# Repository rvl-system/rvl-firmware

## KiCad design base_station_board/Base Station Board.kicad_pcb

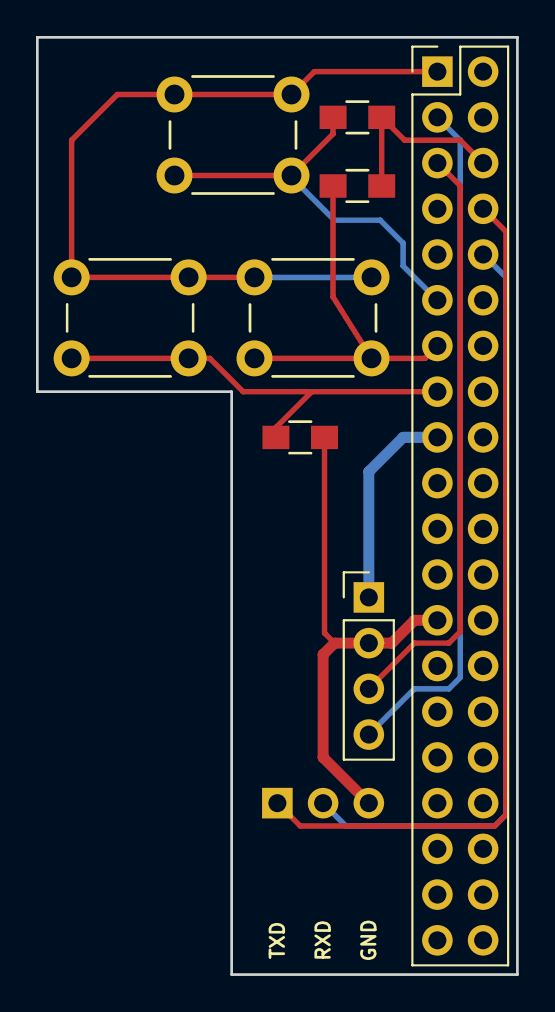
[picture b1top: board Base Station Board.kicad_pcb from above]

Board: 2 copper layers, 26.7 x 52.1 mm, 9 parts (1 on the bottom side), 11 nets.

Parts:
P1: LCD; Pin_Header_Straight_1x04_Pitch2.54mm
P2: Serial; Pin_Header_Angled_1x03_Pitch2.54mm
P3: Raspberry Pi; Pin_Header_Straight_2x20_Pitch2.54mm
R1, R2, R3: 1k; R_0805_HandSoldering
SW1, SW2, SW3: SPST; SW_PUSH_6mm

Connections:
unnamed: P1.1, P3.17
unnamed: P1.2, P2.3, P3.25, R1.2
unnamed: P1.3, P3.5
unnamed: P1.4, P3.3
unnamed: P2.1, P3.8
unnamed: P2.2, P3.10
unnamed: P3.1, SW1.1, SW2.1, SW3.1
unnamed: P3.6, R2.2, R3.2
unnamed: P3.11, R2.1, SW2.2
unnamed: P3.13, R3.1, SW3.2
unnamed: P3.15, R1.1, SW1.2

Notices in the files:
base_station_board/Base Station Board.kicad_pcb:
Copyright Bryan Hughes 2017
